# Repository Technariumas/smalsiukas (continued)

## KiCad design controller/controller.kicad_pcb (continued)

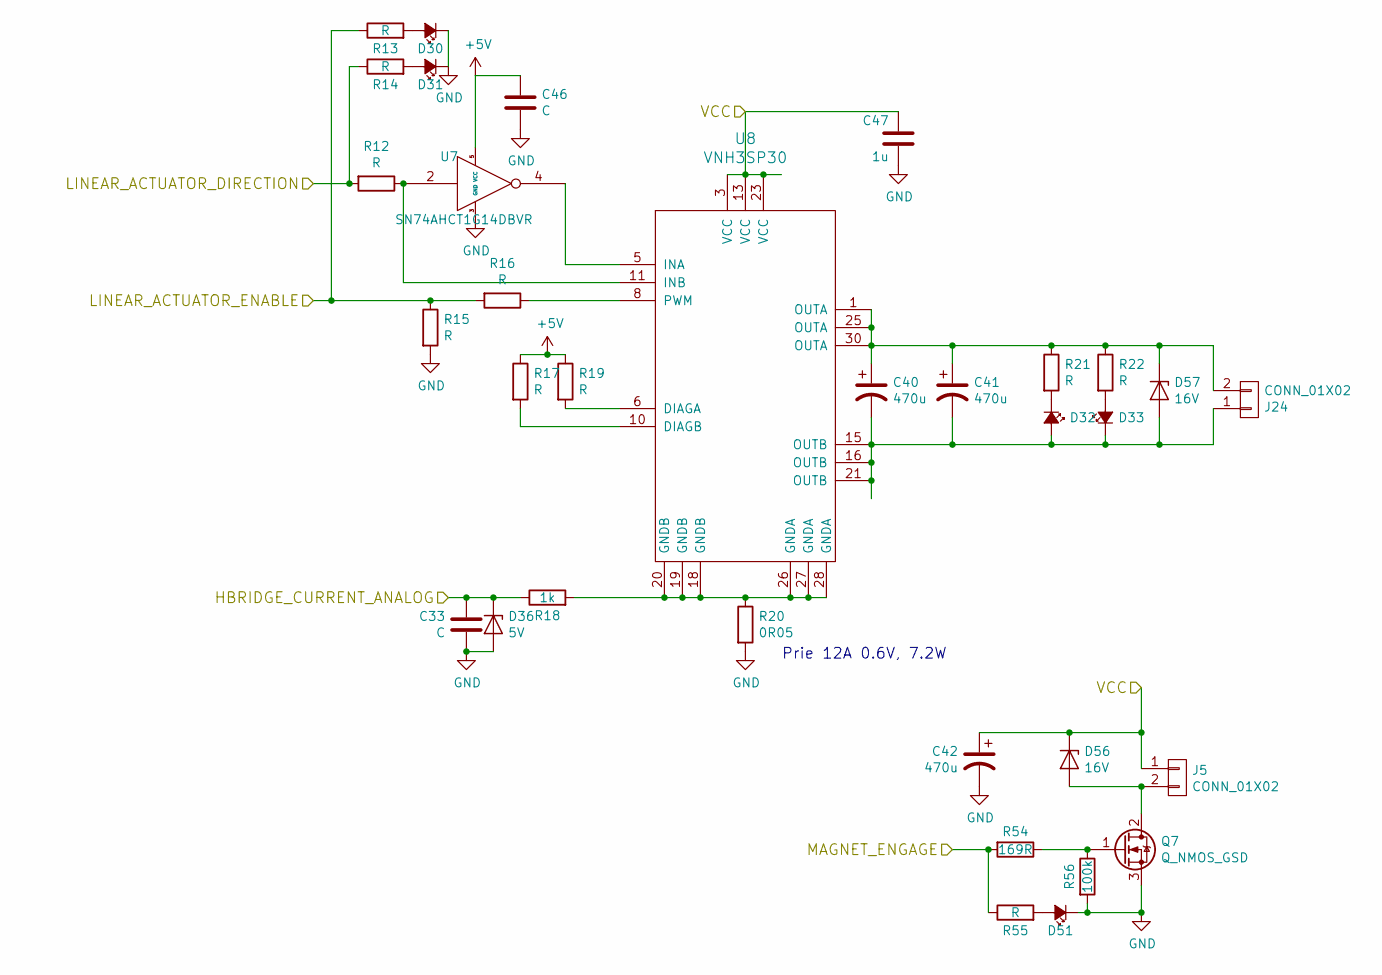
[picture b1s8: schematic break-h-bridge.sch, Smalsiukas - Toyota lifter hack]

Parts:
C33, C46: C; C_0603_HandSoldering
C40, C41, C42: 470u; CP_Radial_D16.0mm_P7.50mm; PartNo ECA2AAM471X
C47: 1u; C_1210_HandSoldering; PartNo ?
D30, D31, D32, D33, D51: LED_Small_ALT; LED_D5.0mm; PartNo ?
D36: 5V; SOD-123; PartNo ?
D56, D57: 16V; D_SMB_Handsoldering; PartNo 1SMB5930BT3G
J5, J24: CONN_01X02; TerminalBlock_5.08-2pol; PartNo ?
Q7: Q_NMOS_GSD; TO-252-2Lead; PartNo ?
R12, R13, R14, R15, R16, R17, R19, R21, R22, R55: R; R_0603_HandSoldering
R18: 1k; R_0603_HandSoldering
R20: 0R05; TO-220-2_Vertical; PartNo ?
R54: 169R; R_0603_HandSoldering
R56: 100k; R_0603_HandSoldering
U7: SN74AHCT1G14DBVR; SOT-23-5_HandSoldering; PartNo SN74LVC1G14DBVR
U8: VNH3SP30; SOIC-30; PartNo ?

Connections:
+5V: C46.1, R17.1, R19.1, U7.5 (VCC); also elsewhere on the board
/Break H bridge/MAGNET_ENGAGE: R54.2, R55.1; also elsewhere on the board
/HBRIDGE_CURRENT_ANALOG: C33.1, D36.1 (K), R18.1; also elsewhere on the board
/LINEAR_ACTUATOR_DIRECTION: R13.1, R15.1, R16.2; also elsewhere on the board
/LINEAR_ACTUATOR_ENABLE: R12.2, R14.1; also elsewhere on the board
GND: C33.2, C42.2, C46.2, C47.2, D30.1 (K), D31.1 (K), D36.2 (A), D51.1 (K), Q7.3 (S), R15.2, R20.2, R56.2, U7.3 (GND); also elsewhere on the board
unnamed: C40.1, C41.1, D57.1 (K), J24.2, R21.1, R22.1, U8.1 (OUTA), U8.25 (OUTA), U8.30 (OUTA), U8.31
unnamed: C40.2, C41.2, D32.2 (A), D33.1 (K), D57.2 (A), J24.1, U8.15 (OUTB), U8.16 (OUTB), U8.21 (OUTB), U8.32
unnamed: D30.2 (A), R13.2
unnamed: D31.2 (A), R14.2
unnamed: D32.1 (K), R21.2
unnamed: D33.2 (A), R22.2
unnamed: D51.2 (A), R55.2
unnamed: D56.2 (A), J5.2, Q7.2 (D)
unnamed: Q7.1 (G), R54.1, R56.1
unnamed: R12.1, U7.2, U8.11 (INB)
unnamed: R16.1, U8.8 (PWM)
unnamed: R17.2, U8.10 (DIAGB)
unnamed: R18.2, R20.1, U8.18 (GNDB), U8.19 (GNDB), U8.20 (GNDB), U8.26 (GNDA), U8.27 (GNDA), U8.28 (GNDA)
unnamed: R19.2, U8.6 (DIAGA)
unnamed: U7.4, U8.5 (INA)
VCC: C42.1, C47.1, D56.1 (K), J5.1, U8.3 (VCC), U8.13 (VCC), U8.23 (VCC), U8.33; also elsewhere on the board

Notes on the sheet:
Prie 12A 0.6V, 7.2W

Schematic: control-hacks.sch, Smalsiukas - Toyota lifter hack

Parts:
C23, C24, C25, C26, C27, C28, C29, C30, C31: C; C_0603_HandSoldering
C43: 470u; CP_Radial_D16.0mm_P7.50mm; PartNo ECA2AAM471X
C44: 1u; C_1210_HandSoldering; PartNo ?
D18, D19, D20, D21, D22, D23, D24, D25, D26: D_ALT; D_SOD-123
D58: 16V; D_SMB_Handsoldering; PartNo 1SMB5930BT3G
K18, K19, K20, K21, K22, K23, K24, K25, K26: RELAY_SEPARATED; Relay_SPDT; PartNo ?

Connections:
/Control Switching/~AUX_ENABLE_PWR: C31.2, D26.2 (A), K26.1; also elsewhere on the board
/Control Switching/~DIR_BACK_ENABLE_PWR: C24.2, D19.2 (A), K19.10; also elsewhere on the board
/Control Switching/~DIR_FWD_ENABLE_PWR: C23.2, D18.2 (A), K18.10; also elsewhere on the board
/Control Switching/~HORN_ENABLE_PWR: C25.2, D20.2 (A), K20.10; also elsewhere on the board
/Control Switching/~KEY_ENABLE_PWR: C28.2, D23.2 (A), K23.1; also elsewhere on the board
/Control Switching/~LIGHTS_ENABLE_PWR: C29.2, D24.2 (A), K24.1; also elsewhere on the board
/Control Switching/~MIRGALKE_ENABLE_PWR: C30.2, D25.2 (A), K25.1; also elsewhere on the board
/Control Switching/~PARKING_DISABLE_PWR: C26.2, D21.2 (A), K21.10; also elsewhere on the board
/Control Switching/~SEAT_ENABLE_PWR: C27.2, D22.2 (A), K22.10; also elsewhere on the board
/ControlHacks/AUX_COMMON: K26.3; also elsewhere on the board
/ControlHacks/AUX_HACK: K26.4; also elsewhere on the board
/ControlHacks/DIR_SW_BACK_HACK: K19.4; also elsewhere on the board
/ControlHacks/DIR_SW_FWD_HACK: K18.4; also elsewhere on the board
/ControlHacks/HORN_SW_HACK: K20.4; also elsewhere on the board
/ControlHacks/KEY_COLD_HACK: K23.4; also elsewhere on the board
/ControlHacks/KEY_HOT_HACK: K23.3; also elsewhere on the board
/ControlHacks/LIGHTS_COMMON: K24.3, K25.3; also elsewhere on the board
/ControlHacks/LIGHTS_HACK: K24.4; also elsewhere on the board
/ControlHacks/MIRGALKE_HACK: K25.4; also elsewhere on the board
/ControlHacks/PARKING_HACK: K21.4; also elsewhere on the board
/ControlHacks/SEAT_GND_HACK: K22.4; also elsewhere on the board
/ControlHacks/SEAT_HACK: K22.3; also elsewhere on the board
/ControlHacks/STEERING_COMMON: K18.3, K19.3, K20.3, K21.3; also elsewhere on the board
/Power/+5V_DIRTY: C23.1, C24.1, C25.1, C26.1, C27.1, C28.1, C29.1, C30.1, C31.1, C43.1, C44.2, D18.1 (K), D19.1 (K), D20.1 (K), D21.1 (K), D22.1 (K), D23.1 (K), D24.1 (K), D25.1 (K), D26.1 (K), D58.1 (K), K18.1, K19.1, K20.1, K21.1, K22.1, K23.10, K24.10, K25.10, K26.10; also elsewhere on the board
GND: C43.2, C44.1, D58.2 (A); also elsewhere on the board

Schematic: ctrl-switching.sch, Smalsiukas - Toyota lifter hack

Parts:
C45: 1u; C_0603_HandSoldering
D35, D37, D38, D39, D42, D43, D44, D45, D46, D47, D48, D49, D50: LED_Small_ALT; LED_D5.0mm; PartNo ?
R23, R24, R25, R26, R28, R29, R30, R32, R33, R34, R35, R36, R37, R38, R39, R40, R41, R69, R70, R71, R72, R73, R74, R75, R76, R77, R78, R79, R80, R81, R82, R83: R; R_0603_HandSoldering
U9: 74HC595_WITH_PWR; SOIC-16_3.9x9.9mm_Pitch1.27mm; PartNo ?
U10, U11: ULN2803A; SOIC-18W_7.5x11.6mm_Pitch1.27mm; PartNo ?

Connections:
+5V: C45.1, U9.10 (SRCLR), U9.16 (VCC); also elsewhere on the board
/Control Switching/AUX_ENABLE: R80.2, U9.5 (QF), U11.6 (I6)
/Control Switching/DIR_BACK_ENABLE: R83.2, U9.7 (QH), U11.8 (I8)
/Control Switching/DIR_FWD_ENABLE: R82.2, U9.6 (QG), U11.7 (I7)
/Control Switching/GAZ_ENABLE: R69.2, U10.2 (I2); also elsewhere on the board
/Control Switching/HORN_ENABLE: R70.2, U9.15 (QA), U11.1 (I1)
/Control Switching/KEY_ENABLE: R32.2, U10.1 (I1); also elsewhere on the board
/Control Switching/LIGHTS_ENABLE: R76.2, U9.3 (QD), U11.4 (I4)
/Control Switching/MIRGALKE_ENABLE: R78.2, U9.4 (QE), U11.5 (I5)
/Control Switching/PARKING_DISABLE: R72.2, U9.1 (QB), U11.2 (I2)
/Control Switching/SEAT_ENABLE: R74.2, U9.2 (QC), U11.3 (I3)
/Control Switching/~AUX_ENABLE_PWR: D48.1 (K), U11.13 (O6); also elsewhere on the board
/Control Switching/~DIR_BACK_ENABLE_PWR: D44.1 (K), U11.15 (O4); also elsewhere on the board
/Control Switching/~DIR_FWD_ENABLE_PWR: D43.1 (K), U11.14 (O5); also elsewhere on the board
/Control Switching/~GAZ_ENABLE_PWR: D42.1 (K), U10.17 (O2); also elsewhere on the board
/Control Switching/~GAZ_SPEED1_PWR: D39.1 (K), U10.14 (O5); also elsewhere on the board
/Control Switching/~GAZ_SPEED2_PWR: D38.1 (K), U10.15 (O4); also elsewhere on the board
/Control Switching/~GAZ_SPEED3_PWR: D37.1 (K), U10.16 (O3); also elsewhere on the board
/Control Switching/~HORN_ENABLE_PWR: D45.1 (K), U11.16 (O3); also elsewhere on the board
/Control Switching/~KEY_ENABLE_PWR: D35.1 (K), U10.18 (O1); also elsewhere on the board
/Control Switching/~LIGHTS_ENABLE_PWR: D50.1 (K), U11.11 (O8); also elsewhere on the board
/Control Switching/~MIRGALKE_ENABLE_PWR: D49.1 (K), U11.12 (O7); also elsewhere on the board
/Control Switching/~PARKING_DISABLE_PWR: D46.1 (K), U11.17 (O2); also elsewhere on the board
/Control Switching/~SEAT_ENABLE_PWR: D47.1 (K), U11.18 (O1); also elsewhere on the board
/GAZ_SPEED1: R75.2, U10.5 (I5); also elsewhere on the board
/GAZ_SPEED2: R73.2, U10.4 (I4); also elsewhere on the board
/GAZ_SPEED3: R71.2, U10.3 (I3); also elsewhere on the board
/Power/+5V_DIRTY: R26.1, R28.1, R29.1, R30.1, R33.1, R34.1, R35.1, R36.1, R37.1, R38.1, R39.1, R40.1, R41.1, U10.10 (COM), U11.10 (COM); also elsewhere on the board
/SPI_CLK: R24.2; also elsewhere on the board
/SPI_DATA: R23.2; also elsewhere on the board
/SPI_LATCH: R25.2; also elsewhere on the board
GND: C45.2, R32.1, R69.1, R70.1, R71.1, R72.1, R73.1, R74.1, R75.1, R76.1, R77.1, R78.1, R79.1, R80.1, R81.1, R82.1, R83.1, U9.8 (GND), U9.13 (G), U10.9 (GND), U11.9 (GND); also elsewhere on the board
unnamed: D35.2 (A), R26.2
unnamed: D37.2 (A), R28.2
unnamed: D38.2 (A), R29.2
unnamed: D39.2 (A), R30.2
unnamed: D42.2 (A), R33.2
unnamed: D43.2 (A), R34.2
unnamed: D44.2 (A), R35.2
unnamed: D45.2 (A), R36.2
unnamed: D46.2 (A), R37.2
unnamed: D47.2 (A), R38.2
unnamed: D48.2 (A), R39.2
unnamed: D49.2 (A), R40.2
unnamed: D50.2 (A), R41.2
unnamed: R23.1, U9.14 (SER)
unnamed: R24.1, U9.11 (SRCLK)
unnamed: R25.1, U9.12 (RCLK)
unnamed: R77.2, U10.6 (I6)
unnamed: R79.2, U10.7 (I7)
unnamed: R81.2, U10.8 (I8)

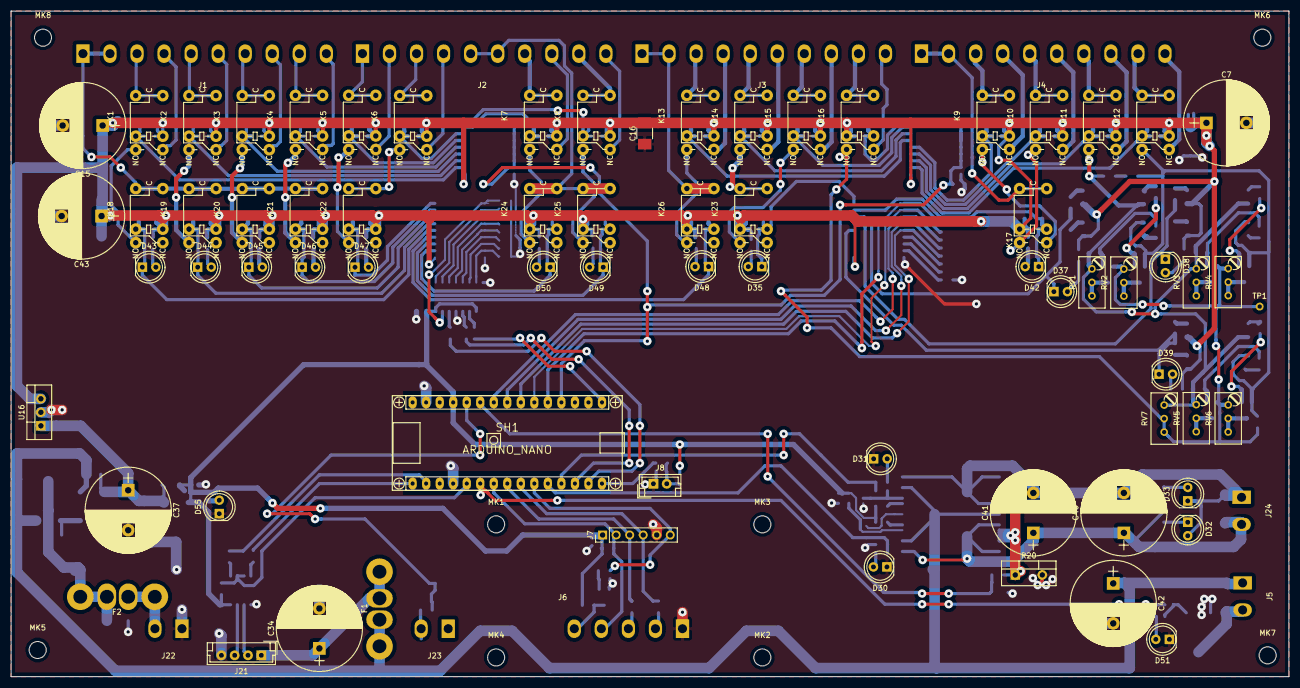
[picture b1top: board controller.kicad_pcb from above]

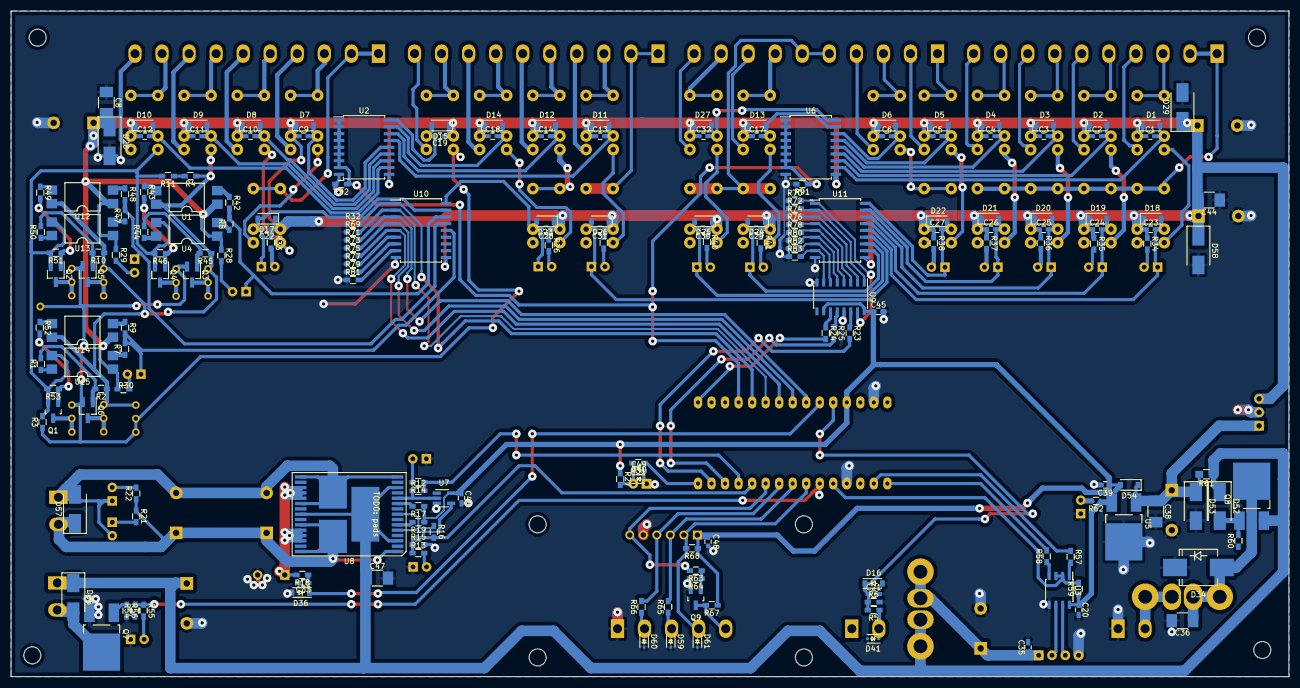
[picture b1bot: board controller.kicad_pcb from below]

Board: 2 copper layers, 240.0 x 125.0 mm, 277 parts (190 on the bottom side), 190 nets.

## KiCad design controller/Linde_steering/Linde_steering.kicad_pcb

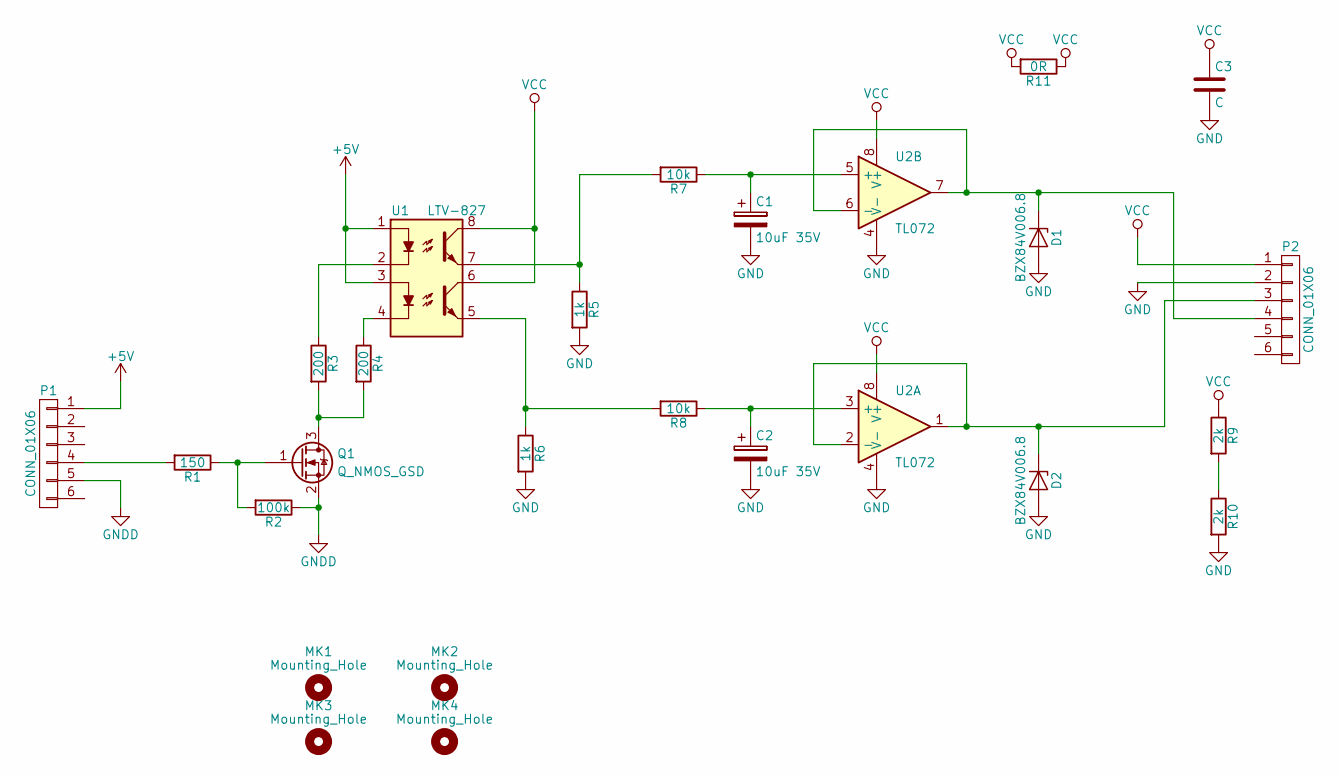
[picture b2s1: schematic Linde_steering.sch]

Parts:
C1, C2: 10uF 35V; CP_Elec_5x5.7
C3: C; R_1206_HandSoldering
D1, D2: BZX84V006.8; SOT-23
MK1, MK2, MK3, MK4: Mounting_Hole; MountingHole_3.2mm_M3_Pad
P1: CONN_01X06; Socket_Strip_Straight_1x06_Pitch2.54mm
P2: CONN_01X06; TerminalBlock_5.08-6pol
Q1: Q_NMOS_GSD
R1: 150; R_0805_HandSoldering
R2: 100k; R_0805_HandSoldering
R3, R4: 200; R_0805_HandSoldering
R5, R6: 1k; R_0805_HandSoldering
R7, R8: 10k; R_0805_HandSoldering
R9, R10: 2k; R_0805_HandSoldering
R11: 0R; R_0805_HandSoldering
U1: LTV-827; DIP-8_SMD
U2: TL072; SOIC-8-N

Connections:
+5V: P1.1, U1.1, U1.3
GND: C1.2, C2.2, C3.2, D1.1 (A), D2.1 (A), P2.2, R5.2, R6.2, R10.2, U2.4 (V-)
GNDD: P1.5, Q1.2 (S), R2.1
unnamed: C1.1, R7.1, U2.5 (+)
unnamed: C2.1, R8.1, U2.3 (+)
unnamed: D1.3 (K), P2.4, U2.6 (-), U2.7
unnamed: D2.3 (K), P2.3, U2.1, U2.2 (-)
unnamed: P1.4, R1.2
unnamed: Q1.1 (G), R1.1, R2.2
unnamed: Q1.3 (D), R3.2, R4.2
unnamed: R3.1, U1.2
unnamed: R4.1, U1.4
unnamed: R5.1, R7.2, U1.7
unnamed: R6.1, R8.2, U1.5
unnamed: R9.2, R10.1
VCC: C3.1, P2.1, R9.1, R11.1, R11.2, U1.6, U1.8, U2.8 (V+)

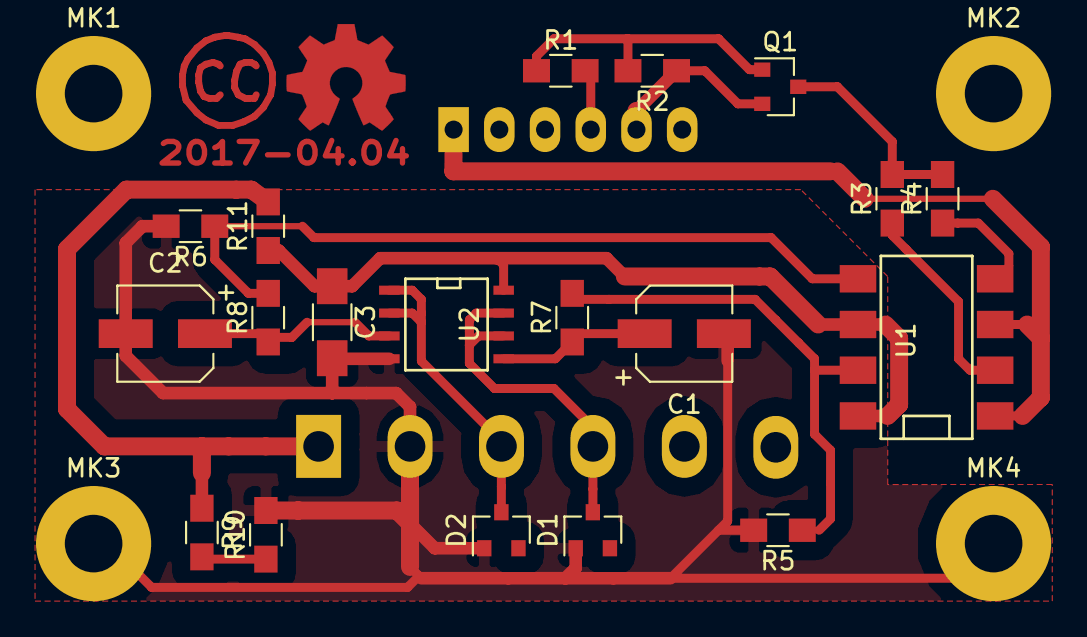
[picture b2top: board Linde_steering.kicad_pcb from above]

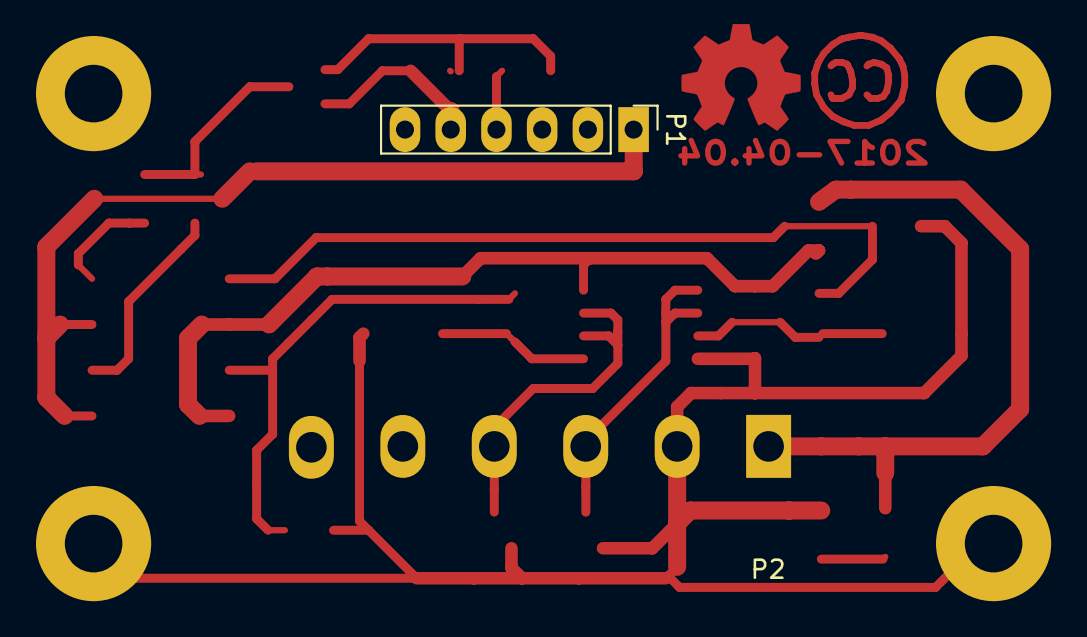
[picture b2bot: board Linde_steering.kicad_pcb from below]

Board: 2 copper layers, 25 parts (2 on the bottom side), 16 nets.

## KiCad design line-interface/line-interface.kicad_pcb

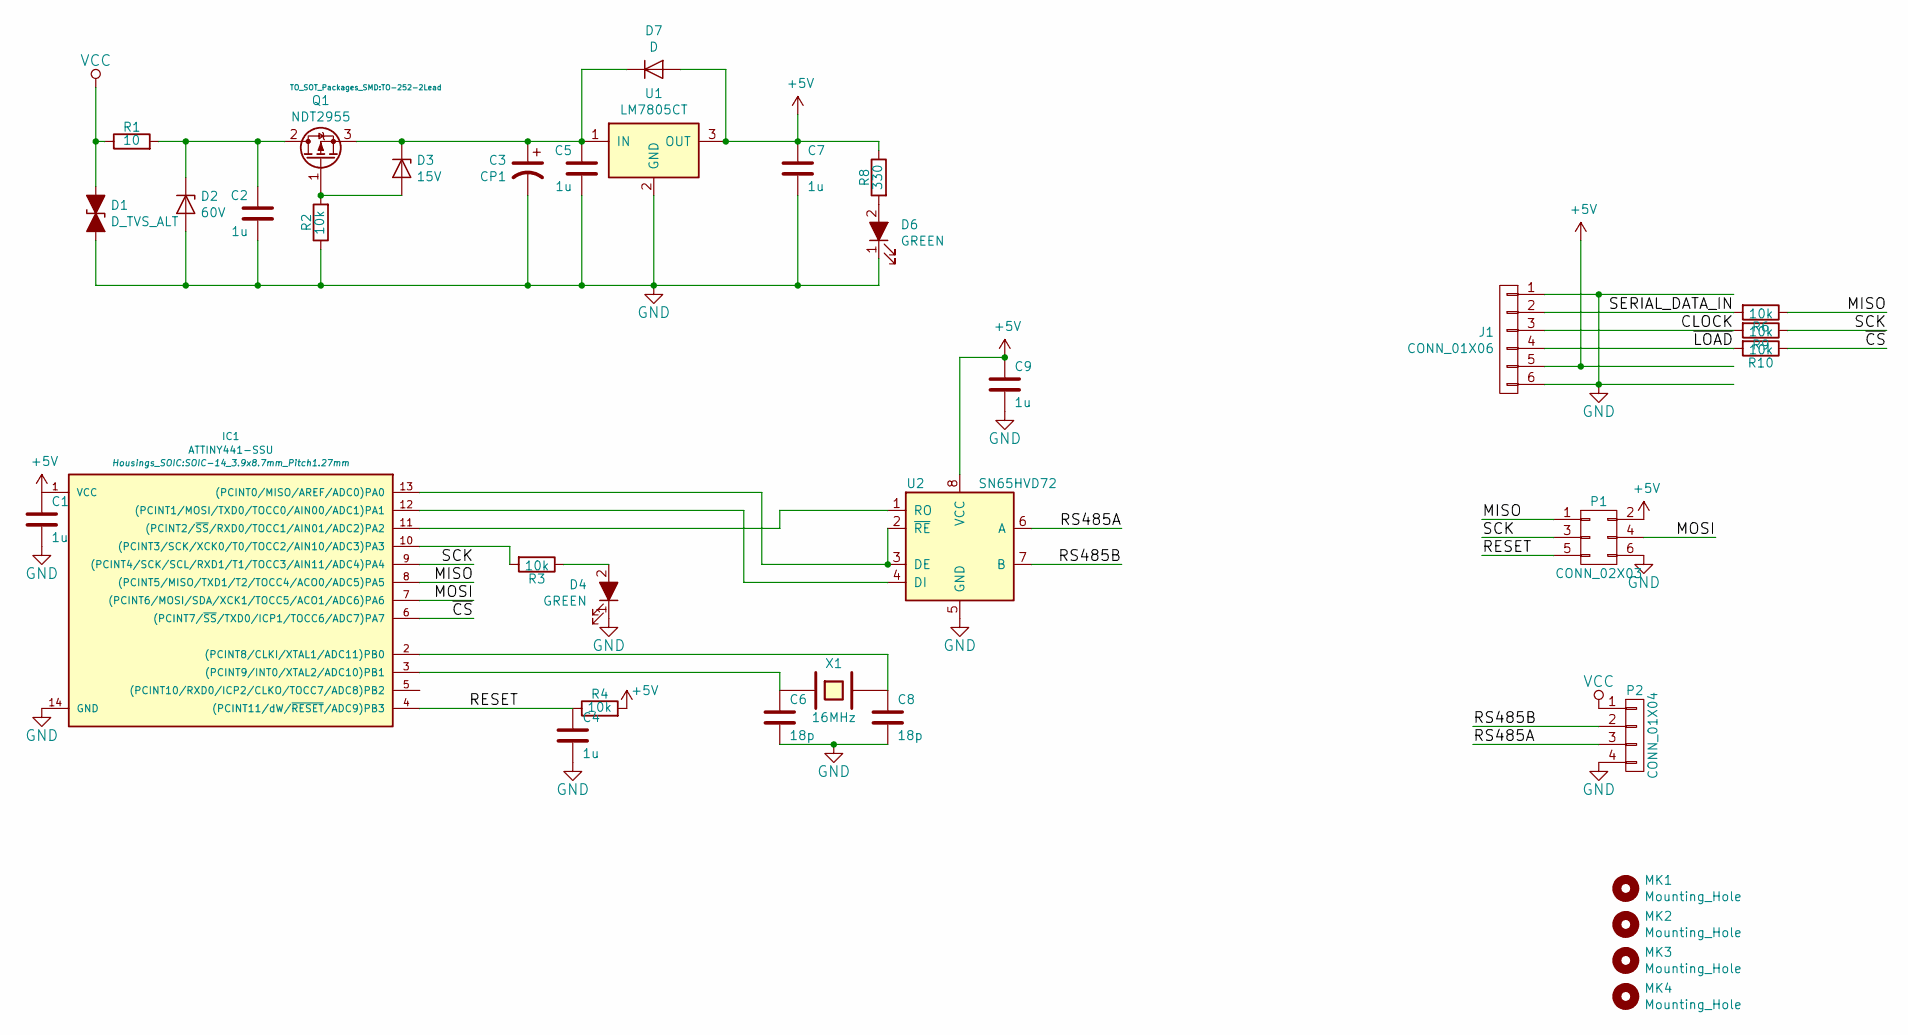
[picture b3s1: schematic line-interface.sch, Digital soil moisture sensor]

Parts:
C1, C4, C7, C9: 1u; C_0603
C2, C5: 1u; C_1210_HandSoldering; PartNo ?
C3: CP1; CP_Radial_D8.0mm_P3.50mm; PartNo ?
C6, C8: 18p; C_0603
D1: D_TVS_ALT; Diode-SMC_Handsoldering; PartNo 1.5SMCJ48CA
D2: 60V; D_SMB_Handsoldering; PartNo 1SMB5944BT3G
D3: 15V; SOD-123; PartNo KDZVTR15B
D4, D6: GREEN; LED_0603; PartNo ?
D7: D; D_SOD-123; PartNo ?
IC1: ATTINY441-SSU; SOIC-14_3.9x8.7mm_Pitch1.27mm; PartNo ?
J1: CONN_01X06; Pin_Header_Straight_1x06_Pitch2.54mm; PartNo ?
MK1, MK2, MK3, MK4: Mounting_Hole; MountingHole_3.2mm_M3; PartNo ?
P1: CONN_02X03; Pin_Header_Straight_2x03_Pitch2.54mm; PartNo ?
P2: CONN_01X04; Pin_Header_Straight_1x04_Pitch2.54mm; PartNo ?
Q1: NDT2955; TO-252-2Lead; PartNo IRFR5410TRPBF
R1: 10; R_0805_HandSoldering; PartNo ?
R2, R3, R4, R6, R9, R10: 10k; R_0603
R8: 330; R_0603
U1: LM7805CT; TO-220_Horizontal; PartNo ?
U2: SN65HVD72; SOIC-8_3.9x4.9mm_Pitch1.27mm; PartNo MAX13442EASA
X1: 16MHz; Crystal_HC49-SD_SMD

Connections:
+5V: C1.1, C7.1, C9.1, D7.2 (A), IC1.1 (VCC), J1.5, P1.2, R4.2, R8.1, U1.3 (OUT), U2.8 (VCC)
/CLOCK: J1.3, R9.2
/MISO: IC1.8 ((PCINT5/MISO/TXD1/T2/TOCC4/ACO0/ADC5)PA5), P1.1, R6.1
/MOSI: IC1.7 ((PCINT6/MOSI/SDA/XCK1/TOCC5/ACO1/ADC6)P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), P1.4
/RESET: C4.1, IC1.4 ((PCINT11/dW/~RESET~/ADC9)PB3), P1.5, R4.1
/RS485A: P2.3, U2.6 (A)
/RS485B: P2.2, U2.7 (B)
/SCK: IC1.9 ((PCINT4/SCK/SCL/RXD1/T1/TOCC3/AIN11/ADC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), P1.3, R9.1
/SERIAL_DATA_IN: J1.2, R6.2
/~CS: IC1.6 ((PCINT7/~SS~/TXD0/ICP1/TOCC6/ADC7)PA7), R10.1
/~LOAD: J1.4, R10.2
GND: C1.2, C2.2, C3.2, C4.2, C5.2, C6.2, C7.2, C8.2, C9.2, D1.2 (A2), D2.2 (A), D4.1 (K), D6.1 (K), IC1.14 (GND), J1.1, J1.6, P1.6, P2.4, R2.1, U1.2 (GND), U2.5 (GND)
unnamed: C2.1, D2.1 (K), Q1.2 (D), R1.2
unnamed: C3.1, C5.1, D3.1 (K), D7.1 (K), Q1.3 (S), U1.1 (IN)
unnamed: C6.1, IC1.3 ((PCINT9/INT0/XTAL2/ADC10)PB1), X1.1
unnamed: C8.1, IC1.2 ((PCINT8/CLKI/XTAL1/ADC11)PB0), X1.2
unnamed: D3.2 (A), Q1.1 (G), R2.2
unnamed: D4.2 (A), R3.1
unnamed: D6.2 (A), R8.2
unnamed: IC1.10 ((PCINT3/SCK/XCK0/T0/TOCC2/AIN10/ADC3)PA3), R3.2
unnamed: IC1.11 ((PCINT2/~SS~/RXD0/TOCC1/AIN01/ADC2)PA2), U2.1 (RO)
unnamed: IC1.12 ((PCINT1/MOSI/TXD0/TOCC0/AIN00/ADC1)PA1), U2.4 (DI)
unnamed: IC1.13 ((PCINT0/MISO/AREF/ADC0)PA0), U2.2 (~RE~), U2.3 (DE)
VCC: D1.1 (A1), P2.1, R1.1

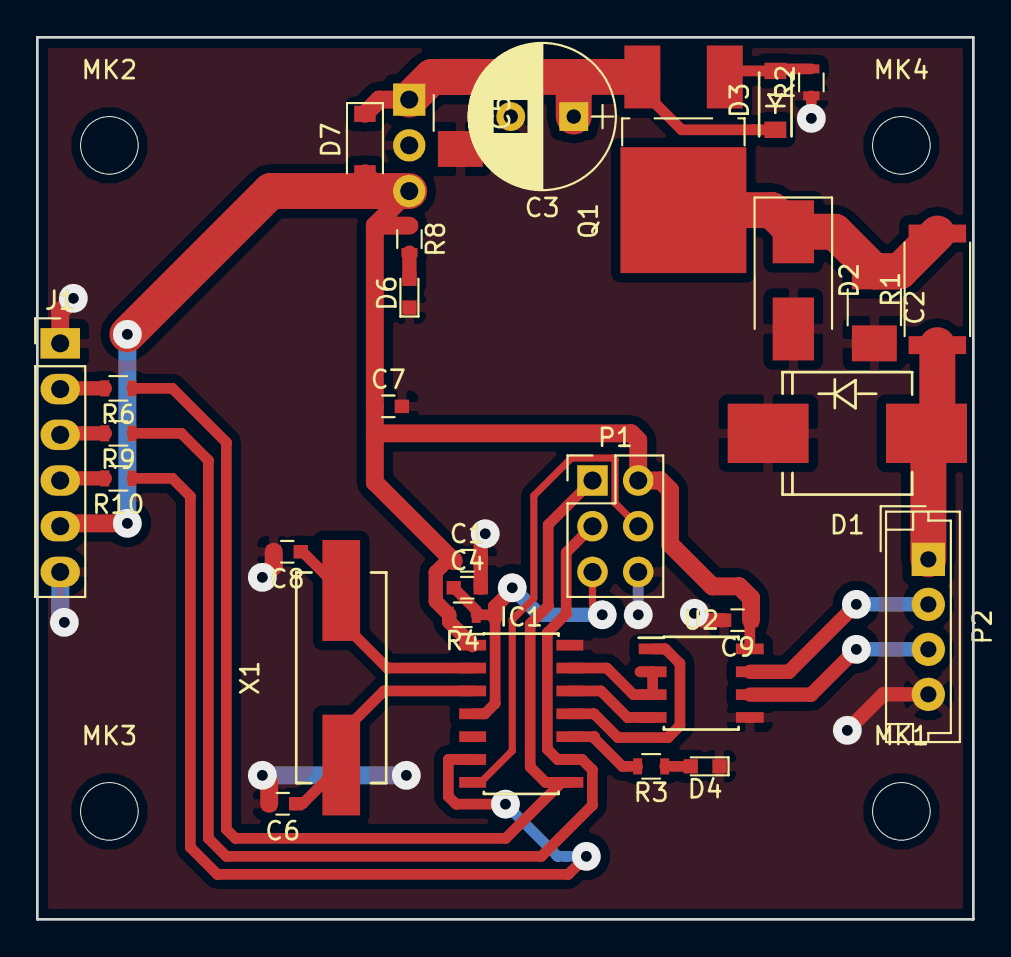
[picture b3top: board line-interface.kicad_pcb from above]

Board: 2 copper layers, 52.0 x 49.0 mm, 35 parts (1 on the bottom side), 24 nets.

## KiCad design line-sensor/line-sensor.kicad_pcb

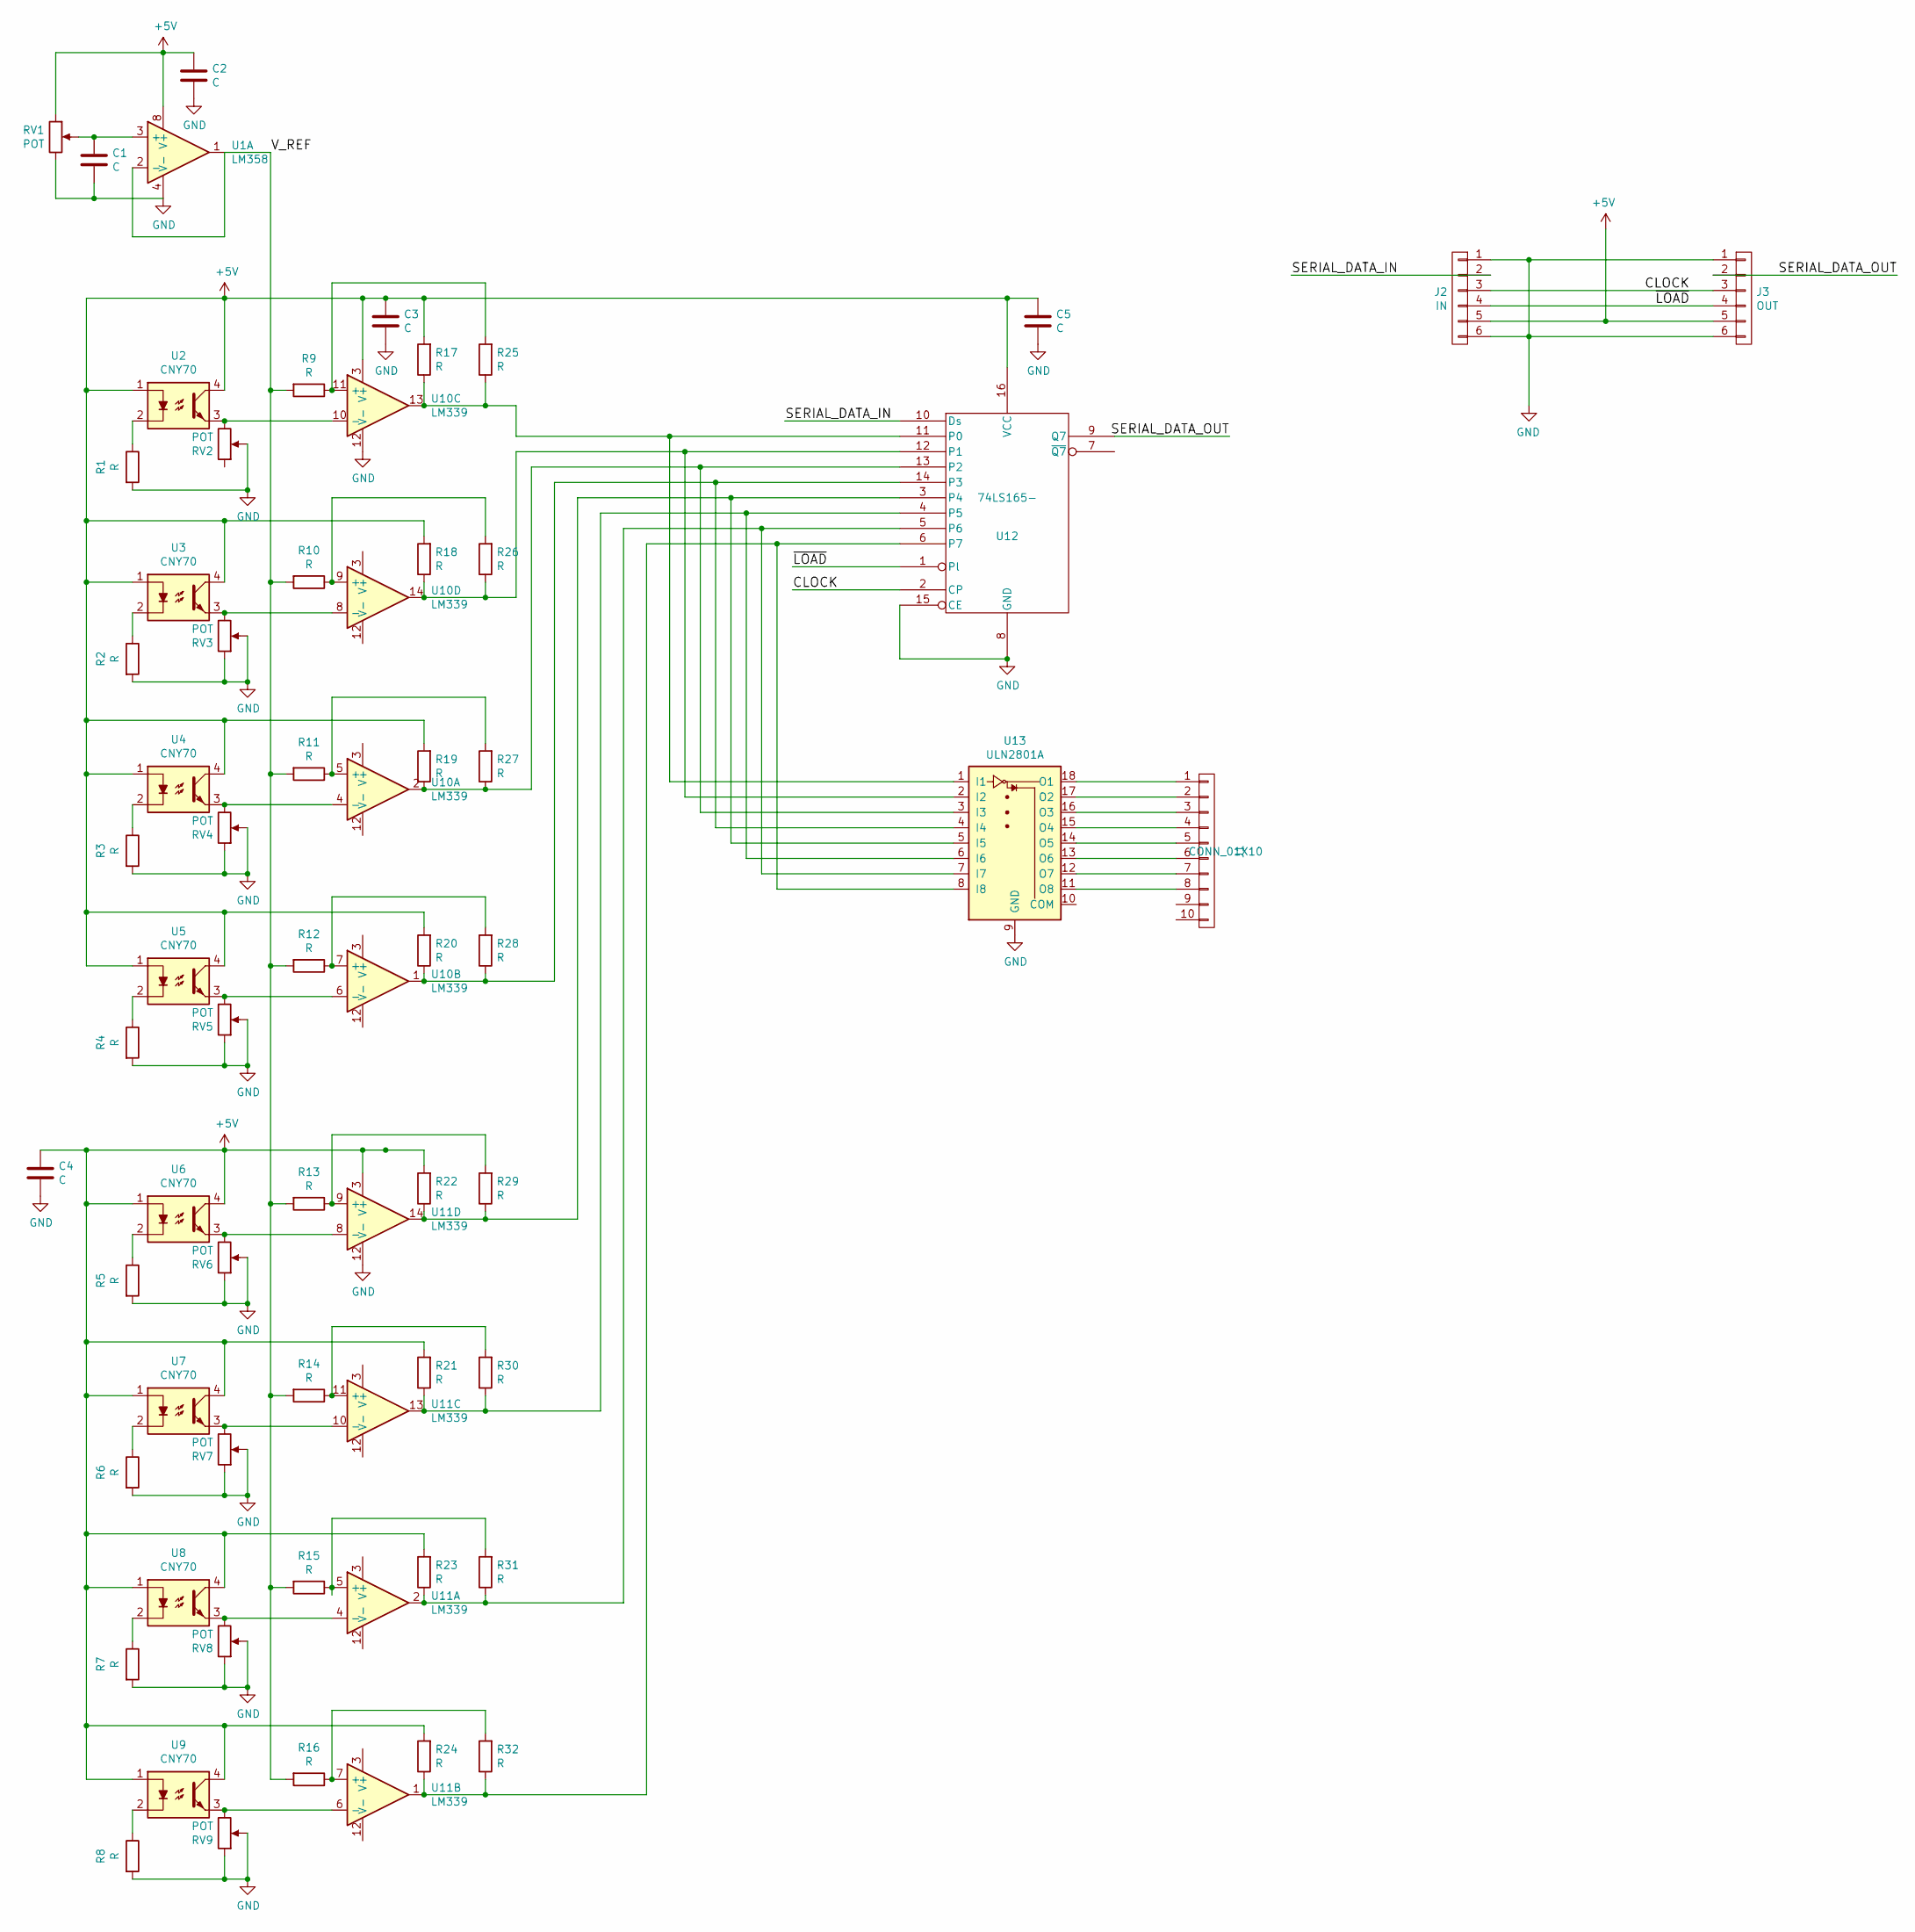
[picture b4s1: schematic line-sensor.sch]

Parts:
C1, C2, C3, C4, C5: C; C_0603_HandSoldering; PartNo ?
J1: CONN_01X10; Multicomp_MC9A12-1034_2x05x2.54mm_Straight; PartNo ?
J2: IN; Pin_Header_Straight_1x06_Pitch2.54mm; PartNo ?
J3: OUT; Pin_Header_Straight_1x06_Pitch2.54mm; PartNo ?
R1, R2, R3, R4, R5, R6, R7, R8, R9, R10, R11, R12, R13, R14, R15, R16, R17, R18, R19, R20, R21, R22, R23, R24, R25, R26, R27, R28, R29, R30, R31, R32: R; R_0603_HandSoldering; PartNo ?
RV1, RV2, RV3, RV4, RV5, RV6, RV7, RV8, RV9: POT; Potentiometer_Trimmer_Bourns_3006W; PartNo ?
U1: LM358; SOIC-8_3.9x4.9mm_Pitch1.27mm; PartNo ?
U2: CNY70; DIP-4_W7.62mm_LongPads; PartNo CNY70
U3, U4, U5, U6, U7, U8, U9: CNY70; DIP-4_W7.62mm; PartNo CNY70
U10, U11: LM339; SOIC-14_3.9x8.7mm_Pitch1.27mm; PartNo ?
U12: 74LS165-; SOIC-16_3.9x9.9mm_Pitch1.27mm; PartNo ?
U13: ULN2801A; SOIC-18W_7.5x11.6mm_Pitch1.27mm; PartNo ?

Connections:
+5V: C2.1, C3.1, C4.1, C5.1, J2.5, J3.5, R17.2, R18.2, R19.2, R20.2, R21.2, R22.2, R23.2, R24.2, RV1.1, U1.8 (V+), U2.1, U2.4, U3.1, U3.4, U4.1, U4.4, U5.1, U5.4, U6.1, U6.4, U7.1, U7.4, U8.1, U8.4, U9.1, U9.4, U10.3 (V+), U11.3 (V+), U12.16 (VCC)
/CLOCK: J2.3, J3.3, U12.2 (CP)
/SERIAL_DATA_IN: J2.2, U12.10 (Ds)
/SERIAL_DATA_OUT: J3.2, U12.9 (Q7)
/V_REF: R9.2, R10.2, R11.2, R12.2, R13.2, R14.2, R15.2, R16.2, U1.1, U1.2 (-)
/~LOAD: J2.4, J3.4, U12.1 (Pl)
GND: C1.2, C2.2, C3.2, C4.2, C5.2, J2.1, J2.6, J3.1, J3.6, R1.2, R2.2, R3.2, R4.2, R5.2, R6.2, R7.2, R8.2, RV1.3, RV2.2, RV3.1, RV3.2, RV4.1, RV4.2, RV5.1, RV5.2, RV6.1, RV6.2, RV7.1, RV7.2, RV8.1, RV8.2, RV9.1, RV9.2, U1.4 (V-), U10.12 (V-), U11.12 (V-), U12.8 (GND), U12.15 (CE), U13.9 (GND)
unnamed: C1.1, RV1.2, U1.3 (+)
unnamed: J1.1, U13.18 (O1)
unnamed: J1.2, U13.17 (O2)
unnamed: J1.3, U13.16 (O3)
unnamed: J1.4, U13.15 (O4)
unnamed: J1.5, U13.14 (O5)
unnamed: J1.6, U13.13 (O6)
unnamed: J1.7, U13.12 (O7)
unnamed: J1.8, U13.11 (O8)
unnamed: R1.1, U2.2
unnamed: R2.1, U3.2
unnamed: R3.1, U4.2
unnamed: R4.1, U5.2
unnamed: R5.1, U6.2
unnamed: R6.1, U7.2
unnamed: R7.1, U8.2
unnamed: R8.1, U9.2
unnamed: R10.1, R26.2, U10.9 (+)
unnamed: R11.1, R27.2, U10.5 (+)
unnamed: R12.1, R28.2, U10.7 (+)
unnamed: R13.1, R29.2, U11.9 (+)
unnamed: R14.1, R30.2, U11.11 (+)
unnamed: R15.1, R31.2, U11.5 (+)
unnamed: R16.1, R32.2, U11.7 (+)
unnamed: R17.1, R25.1, U10.13, U12.11 (P0), U13.1 (I1)
unnamed: R18.1, R26.1, U10.14, U12.12 (P1), U13.2 (I2)
unnamed: R19.1, R27.1, U10.2, U12.13 (P2), U13.3 (I3)
unnamed: R20.1, R28.1, U10.1, U12.14 (P3), U13.4 (I4)
unnamed: R21.1, R30.1, U11.13, U12.4 (P5), U13.6 (I6)
unnamed: R22.1, R29.1, U11.14, U12.3 (P4), U13.5 (I5)
unnamed: R23.1, R31.1, U11.2, U12.5 (P6), U13.7 (I7)
unnamed: R24.1, R32.1, U11.1, U12.6 (P7), U13.8 (I8)
unnamed: R9.1, R25.2, U10.11 (+)
unnamed: RV2.3, U2.3, U10.10 (-)
unnamed: RV3.3, U3.3, U10.8 (-)
unnamed: RV4.3, U4.3, U10.4 (-)
unnamed: RV5.3, U5.3, U10.6 (-)
unnamed: RV6.3, U6.3, U11.8 (-)
unnamed: RV7.3, U7.3, U11.10 (-)
unnamed: RV8.3, U8.3, U11.4 (-)
unnamed: RV9.3, U9.3, U11.6 (-)

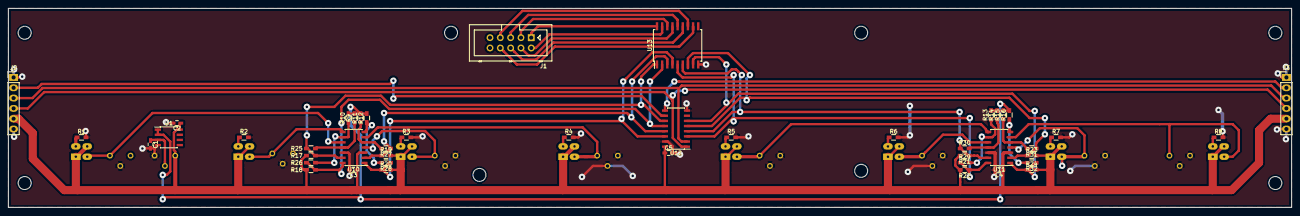
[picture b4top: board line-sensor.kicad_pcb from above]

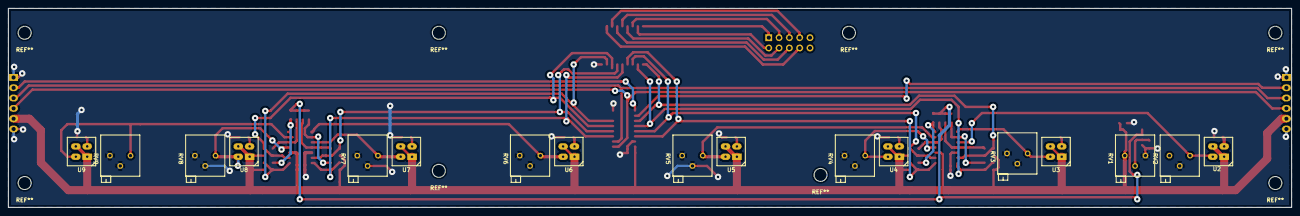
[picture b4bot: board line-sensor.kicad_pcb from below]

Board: 2 copper layers, 316.0 x 49.0 mm, 62 parts (17 on the bottom side), 48 nets.
